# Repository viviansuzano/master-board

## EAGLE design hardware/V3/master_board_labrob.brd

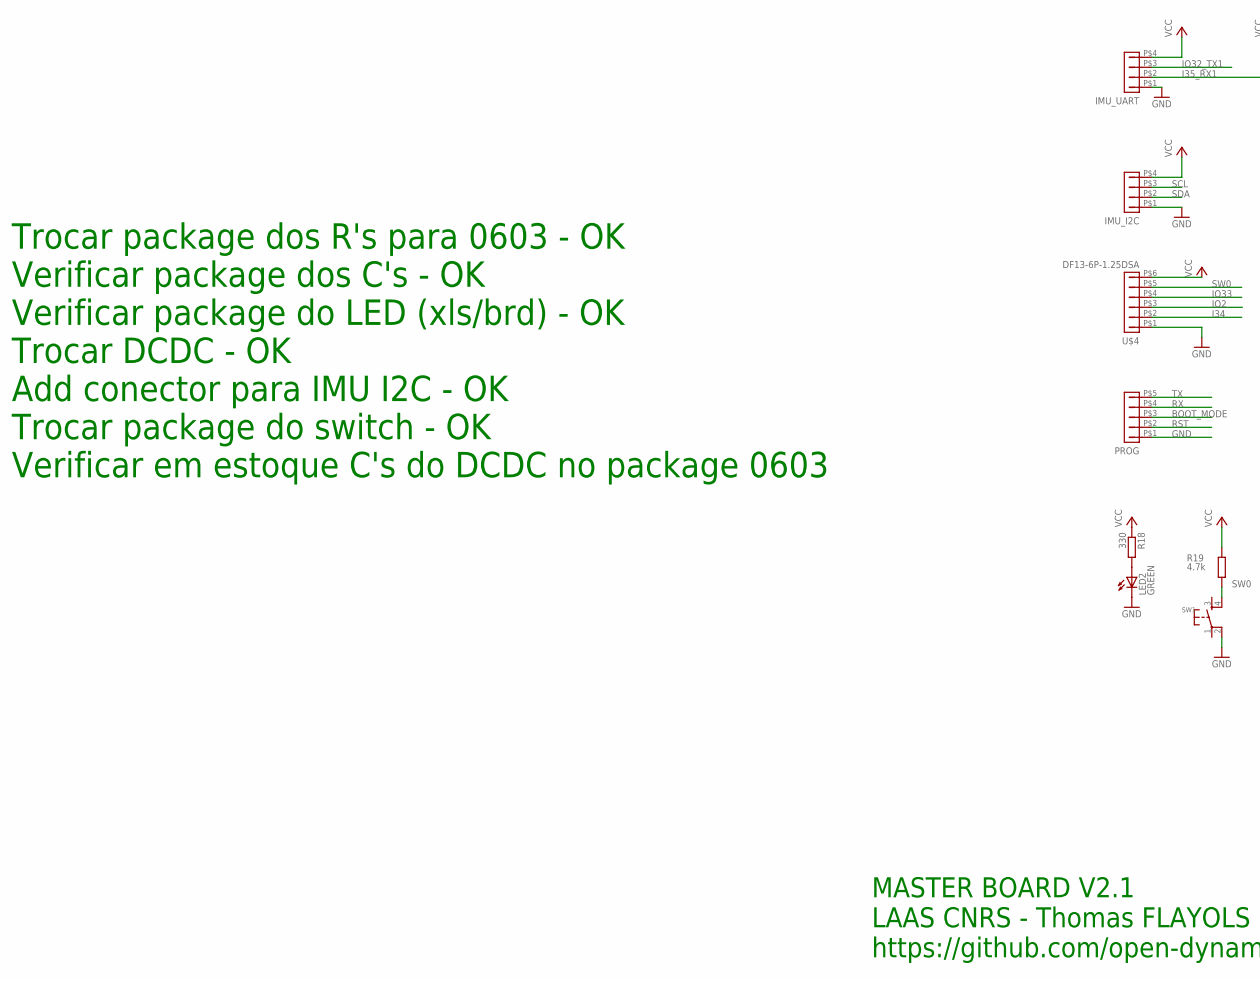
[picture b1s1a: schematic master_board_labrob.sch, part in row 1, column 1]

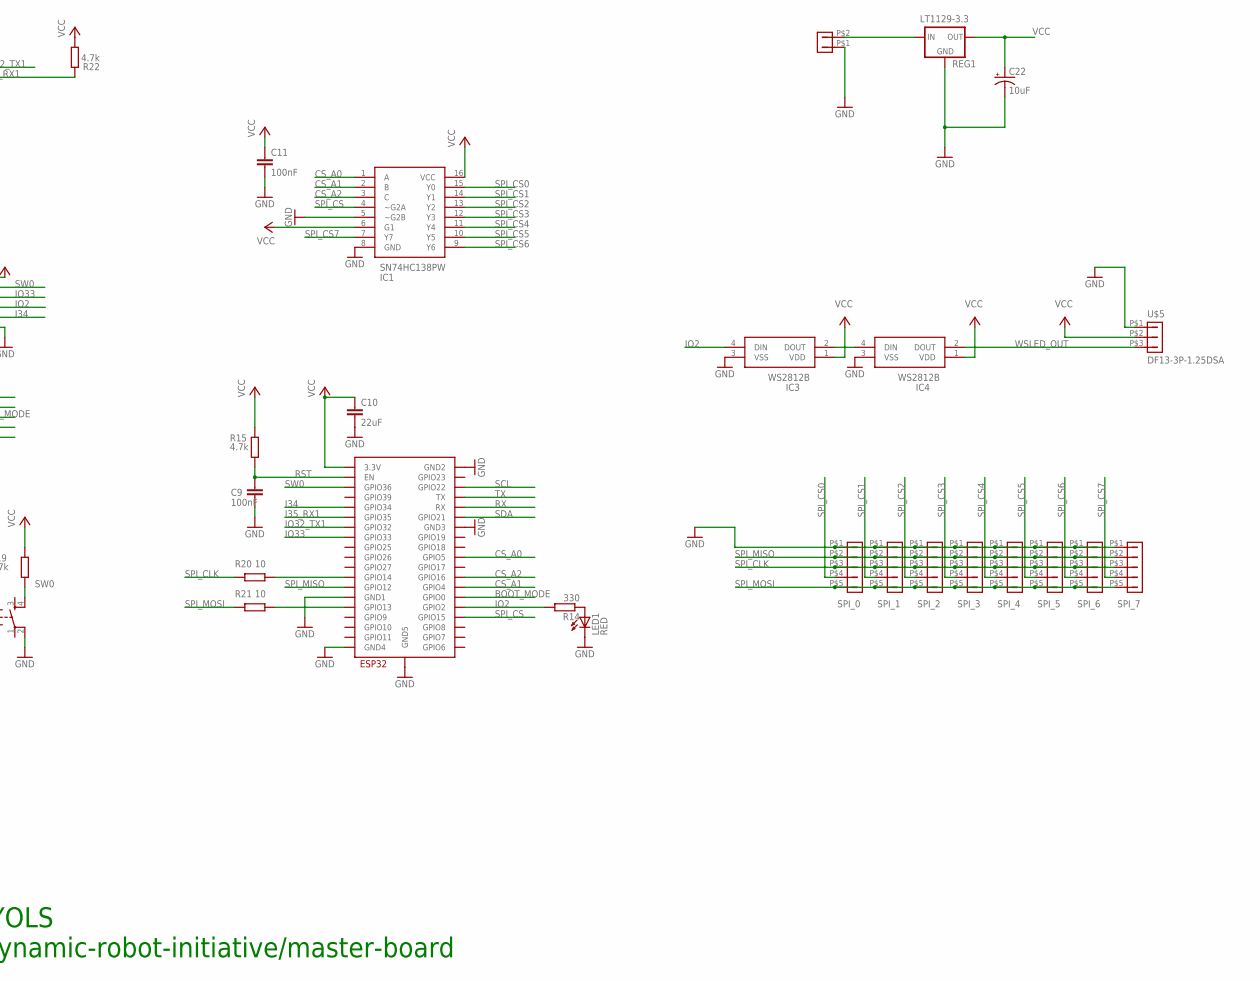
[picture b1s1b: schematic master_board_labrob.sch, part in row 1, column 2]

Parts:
C9, C11: 100nF; C0603; MANUFACTURER_PART_NUMBER CPL-CAP-X7R-0402-100NF-16V
C10: 22uF; C0805; MANUFACTURER_PART_NUMBER CPL-CAP-X5R-0805-22UF-6.3V
C22: 10uF; C/6032-28R
IC1: SN74HC138PW; SOP65P640X120-16N
IC3, IC4: WS2812B
IMU_I2C: DF13-4P-1.25DSA; MANUFACTURER_PART_NUMBER DF13-4P-1.25DSA
IMU_UART: DF13-4P-1.25DSA; MANUFACTURER_PART_NUMBER DF13-4P-1.25DSA
LED1: RED; CHIPLED_0603; MANUFACTURER_PART_NUMBER CPL-LED-0603-RED
LED2: GREEN; CHIPLED_0603; MANUFACTURER_PART_NUMBER CPL-LED-0603-GREEN
POWER: DF13-2P-1.25DSA; MANUFACTURER_PART_NUMBER DF13-3P-1.25DSA
PROG: DF13-5P-1.25DSA; MANUFACTURER_PART_NUMBER DF13-5P-1.25DSA
R14, R18: 330; R0603; MANUFACTURER_PART_NUMBER RC0402JR-13330RL
R15, R19, R22: 4.7k; R0603; MANUFACTURER_PART_NUMBER CPL-RES-0402-4.7K-0.063W
R20, R21: 10; R0603; MANUFACTURER_PART_NUMBER CPL-RES-0402-10-0.063W
REG1: LT1129-3.3; SOT223
SPI_0, SPI_1, SPI_2, SPI_3, SPI_4, SPI_5, SPI_6, SPI_7: DF13-5P-1.25DSA; MANUFACTURER_PART_NUMBER DF13-5P-1.25DSA
SW1: B3U-1000P-2P-SMD; DTSM-6; MANUFACTURER_PART_NUMBER B3U-1000P
U$1: ESP32-WROOM; MANUFACTURER_PART_NUMBER ESP32-WROOM-32D
U$4: DF13-6P-1.25DSA; MANUFACTURER_PART_NUMBER DF13-6P-1.25DSA
U$5: DF13-3P-1.25DSA; MANUFACTURER_PART_NUMBER DF13-3P-1.25DSA

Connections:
BOOT_MODE: PROG.P$3 (3), U$1.IO0 (GPIO0)
CS_A0: IC1.1 (A), U$1.IO5 (GPIO5)
CS_A1: IC1.2 (B), U$1.IO4 (GPIO4)
CS_A2: IC1.3 (C), U$1.IO16 (GPIO16)
GND: C9.2, C10.2, C11.2, C22.-, IC1.5 (~G2B), IC1.8 (GND), IC3.3 (VSS), IC4.3 (VSS), IMU_I2C.P$1 (1), IMU_UART.P$1 (1), LED1.C, LED2.C, POWER.P$1 (1), PROG.P$1 (1), REG1.2 (GND), REG1.TAB (GND), SPI_0.P$1 (1), SPI_1.P$1 (1), SPI_2.P$1 (1), SPI_3.P$1 (1), SPI_4.P$1 (1), SPI_5.P$1 (1), SPI_6.P$1 (1), SPI_7.P$1 (1), SW1.2, U$1.GND1, U$1.GND2, U$1.GND3, U$1.GND4, U$1.GND5, U$4.P$1 (1), U$5.P$1 (1)
I34: U$1.IO34 (GPIO34), U$4.P$2 (2)
I35_RX1: IMU_UART.P$2 (2), R22.2, U$1.IO35 (GPIO35)
IO2: IC3.4 (DIN), R14.2, U$1.IO2 (GPIO2), U$4.P$3 (3)
IO32_TX1: IMU_UART.P$3 (3), U$1.IO32 (GPIO32)
IO33: U$1.IO33 (GPIO33), U$4.P$4 (4)
unnamed: IC3.2 (DOUT), IC4.4 (DIN)
unnamed: POWER.P$2 (2), REG1.1 (IN)
unnamed: LED1.A, R14.1
unnamed: R21.2, U$1.IO13 (GPIO13)
unnamed: LED2.A, R18.2
unnamed: R20.2, U$1.IO14 (GPIO14)
RST: C9.1, PROG.P$2 (2), R15.1, U$1.EN
RX: PROG.P$4 (4), U$1.RX
SCL: IMU_I2C.P$3 (3), U$1.IO22 (GPIO22)
SDA: IMU_I2C.P$2 (2), U$1.IO21 (GPIO21)
SPI_CLK: R20.1, SPI_0.P$3 (3), SPI_1.P$3 (3), SPI_2.P$3 (3), SPI_3.P$3 (3), SPI_4.P$3 (3), SPI_5.P$3 (3), SPI_6.P$3 (3), SPI_7.P$3 (3)
SPI_CS: IC1.4 (~G2A), U$1.IO15 (GPIO15)
SPI_CS0: IC1.15 (Y0), SPI_0.P$4 (4)
SPI_CS1: IC1.14 (Y1), SPI_1.P$4 (4)
SPI_CS2: IC1.13 (Y2), SPI_2.P$4 (4)
SPI_CS3: IC1.12 (Y3), SPI_3.P$4 (4)
SPI_CS4: IC1.11 (Y4), SPI_4.P$4 (4)
SPI_CS5: IC1.10 (Y5), SPI_5.P$4 (4)
SPI_CS6: IC1.9 (Y6), SPI_6.P$4 (4)
SPI_CS7: IC1.7 (Y7), SPI_7.P$4 (4)
SPI_MISO: SPI_0.P$2 (2), SPI_1.P$2 (2), SPI_2.P$2 (2), SPI_3.P$2 (2), SPI_4.P$2 (2), SPI_5.P$2 (2), SPI_6.P$2 (2), SPI_7.P$2 (2), U$1.IO12 (GPIO12)
SPI_MOSI: R21.1, SPI_0.P$5 (5), SPI_1.P$5 (5), SPI_2.P$5 (5), SPI_3.P$5 (5), SPI_4.P$5 (5), SPI_5.P$5 (5), SPI_6.P$5 (5), SPI_7.P$5 (5)
SW0: R19.1, SW1.4, U$1.SENSOR_VP (GPIO36), U$4.P$5 (5)
TX: PROG.P$5 (5), U$1.TX
VCC: C10.1, C11.1, C22.+, IC1.6 (G1), IC1.16 (VCC), IC3.1 (VDD), IC4.1 (VDD), IMU_I2C.P$4 (4), IMU_UART.P$4 (4), R15.2, R18.1, R19.2, R22.1, REG1.3 (OUT), U$1.3V3 (3.3V), U$4.P$6 (6), U$5.P$2 (2)
WSLED_OUT: IC4.2 (DOUT), U$5.P$3 (3)

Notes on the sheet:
MASTER BOARD V2.1 LAAS CNRS - Thomas FLAYOLS https://github.com/open-dynamic-robot-initiative/master-board
Trocar package dos R's para 0603 - OK Verificar package dos C's - OK Verificar package do LED (xls/brd) - OK Trocar DCDC - OK Add conector para IMU I2C - OK Trocar package do switch - OK Verificar em estoque C's do DCDC no package 0603

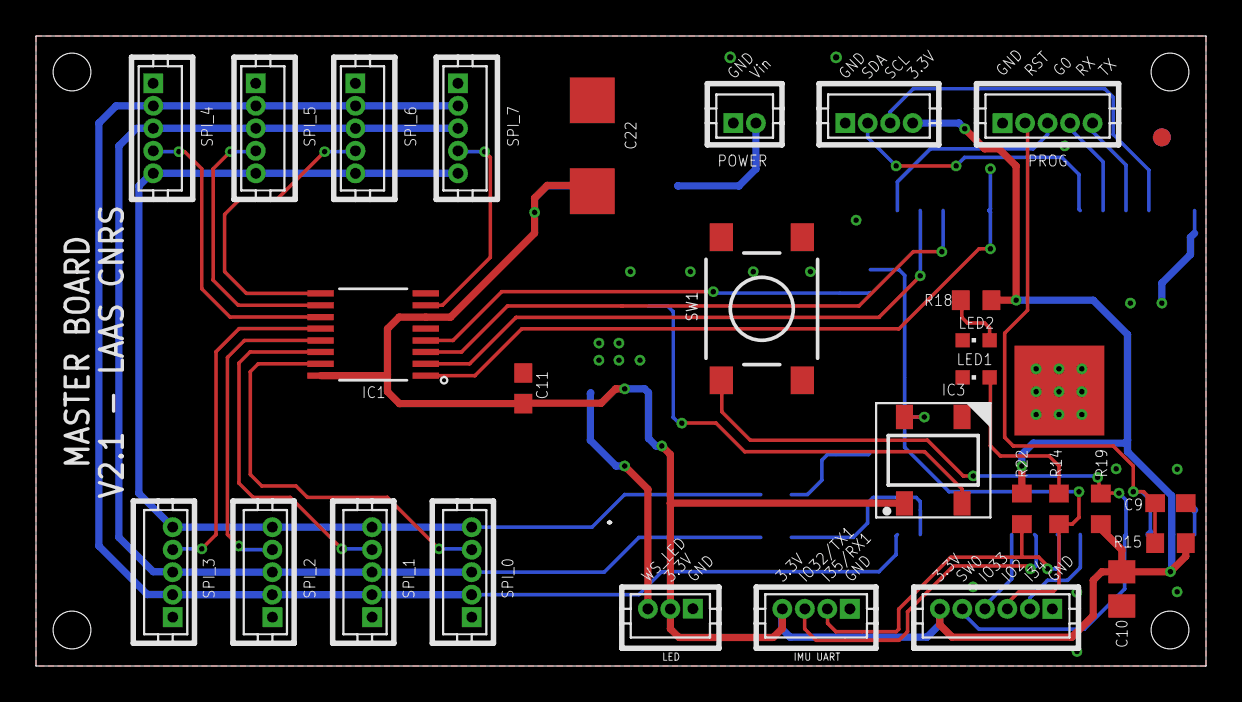
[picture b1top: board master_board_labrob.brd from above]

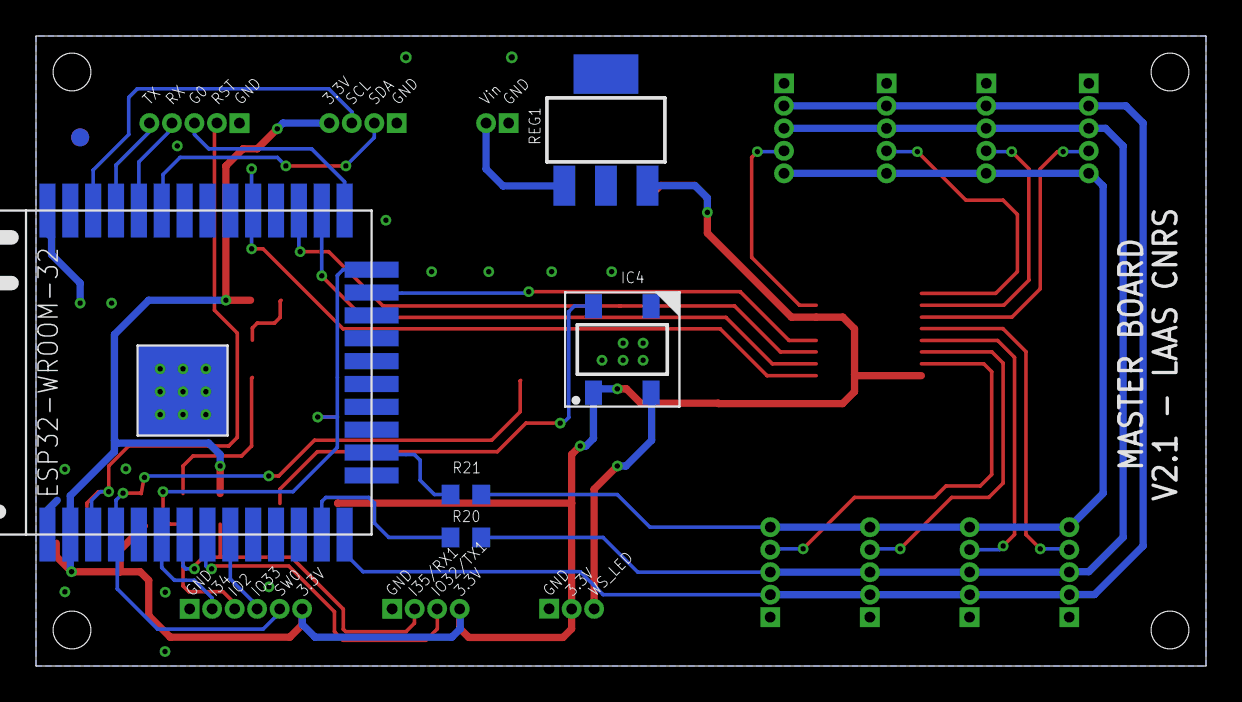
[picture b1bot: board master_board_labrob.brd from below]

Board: 2 copper layers, 65.0 x 35.0 mm, 35 parts (6 on the bottom side), 36 nets.

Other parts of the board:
REF2, REF4: VISION_REF10

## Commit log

2022-05-29 New customized version of the MasterBoard without ethernet communication option.
2022-06-05 Adds a file with instructions for flashing and testing the master-board. Adds an alternative firmware for testing spi communication only.
2022-06-05 Add some debug prints do the sdk functions and updates the mac addresses.

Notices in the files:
parts and their libraries:
dicons: Copyright (C) 2004, Bob Starr (rtzaudio@mindspring.com)
